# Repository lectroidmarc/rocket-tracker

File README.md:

# Rocket Tracker

This is the code for a [model rocket](https://en.wikipedia.org/wiki/Model_rocket) tracking system, to find (lost) model rockets via GPS.

The idea is that a GPS transmitter will live in a rocket and transmit data to a ground station via radio.  That ground station will then update a "cloud" based data store with the location(s) of the rocket(s).  A user (or users) can then access that data with any internet connected device (phone, tablet, laptop etc) to see the locations of their rockets.

Easy.

This system can be used by individuals for tracking one or more rockets or by large groups for tracking larger numbers of rockets.

The system is made up of the following components:

* ##### The GPS Transmitter

  The GPS transmitter is a small microcontroller that connects to a GPS and some kind of [XBee radio](http://www.digi.com/lp/xbee).  The micorcontroller parses the NMEA data from the GPS and transmits location data once per second over the radio.

  Transmission packets are 9 byte packets made up of a status byte then 4 bytes for latitude and 4 bytes for longitude (each are 4 byte floats).

* ##### The Ground Station

  The ground station listens for location messages from the transmitters and then forwards their location to a [Firebase](https://firebase.google.com) based database.

  If ZigBee radios are used, the ground station is also the network coordinator.

  The ground station code itself is a simple [NodeJS](https://nodejs.org/) app and so can run on anything that can run NodeJS and has a serial port to talk to an XBee radio.  And has internet access.

* ##### The Client App

  The client app is what the user uses to see the location of their rocket.  It connects to Firebase and displays the location data in (near) real time and allows the user to open the rocket's location in a mapping app.  Client web app code is located in the [gh-pages branch](../../tree/gh-pages) and can be seen at https://lectroidmarc.github.io/rocket-tracker/.

* ##### Dumb Relays (optional)

  If using ZigBee radios, every GPS transmitter is already a "router" but dedicated routers could also be added to extend range or enhance coverage.  These are simple ZigBee routers node that have no other logic to them, just powered pre-configured radios.

#### XBee Radio Setup

Generally speaking the only thing that needs to be changed from a factory default XBee radio is that they need to be placed into [API Mode 2](http://knowledge.digi.com/articles/Knowledge_Base_Article/What-is-API-Application-Programming-Interface-Mode-and-how-does-it-work).  Everything else can be handled in software.

For [ZigBee](https://en.wikipedia.org/wiki/ZigBee) radios, the proper ZigBee firmware (Coordinator, Router or End Device) will have to be installed.  For our purposes there's no advantage to the "End Device" firmware, so it's just one Coordinator and multiple Routers.

Note: Alternatively, settings (such as the PAN ID) can be pre-configured in each module.  In these cases, comment out the matching settings in the configuration file so they're not overwritten.

##### Dumb Relay nodes

Dumb relay nodes however should be configured in firmware with the PAN ID (`ATID`) and with Channel Verification turned on (`ATJV1`).

#### To Do

* The XBee protocols support status packets so the transmitter can use the lack of a successful status packet as a signal to enable some alternate means of discovery -- like enabling a loud buzzer after a certain timeout.

* Include some sort of built-in internet connectivity in the ground station.

* Expose the location data via a custom Bluetooth LE GATT profile on the ground station and allow the clients in range to use the [Web Bluetooth API](https://webbluetoothcg.github.io/web-bluetooth/) to fetch and display the data.  Note, with Bluetooth, _only one client can connect at a time_.

-30-

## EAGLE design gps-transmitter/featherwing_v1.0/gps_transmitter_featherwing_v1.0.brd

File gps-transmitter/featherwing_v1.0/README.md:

# GPS Transmitter M0 FeatherWing v1.0

These are [Eagle](http://www.autodesk.com/products/eagle/overview) files for a "FeatherWing", basically a sheild, for an [Adafruit Feather M0 Basic Proto](https://www.adafruit.com/products/2772) that supports both a XBee radio and an [Adafruit Ultimate GPS v3](https://www.adafruit.com/products/746).

Additionally the M0 BAT pin is tied to the GPS VBAT pin to enable hot start functionality.

Besides the Feather M0, Ultimate GPS and the appropriate XBee module, the following BOM is needed for a fully functioning FeatherWing

* 1x - [Short Feather Male Headers](https://www.adafruit.com/products/3002)
* 1x - [2mm 10 pin XBee Socket Headers](https://www.adafruit.com/products/366)
* 1x - [Standard 0.1" female headers](https://www.adafruit.com/products/598)
* 1x - [2-pin, 3.5mm pitch, screw terminal](https://www.adafruit.com/products/724)
* 2x56 (or M2) screws for mounting

-30-

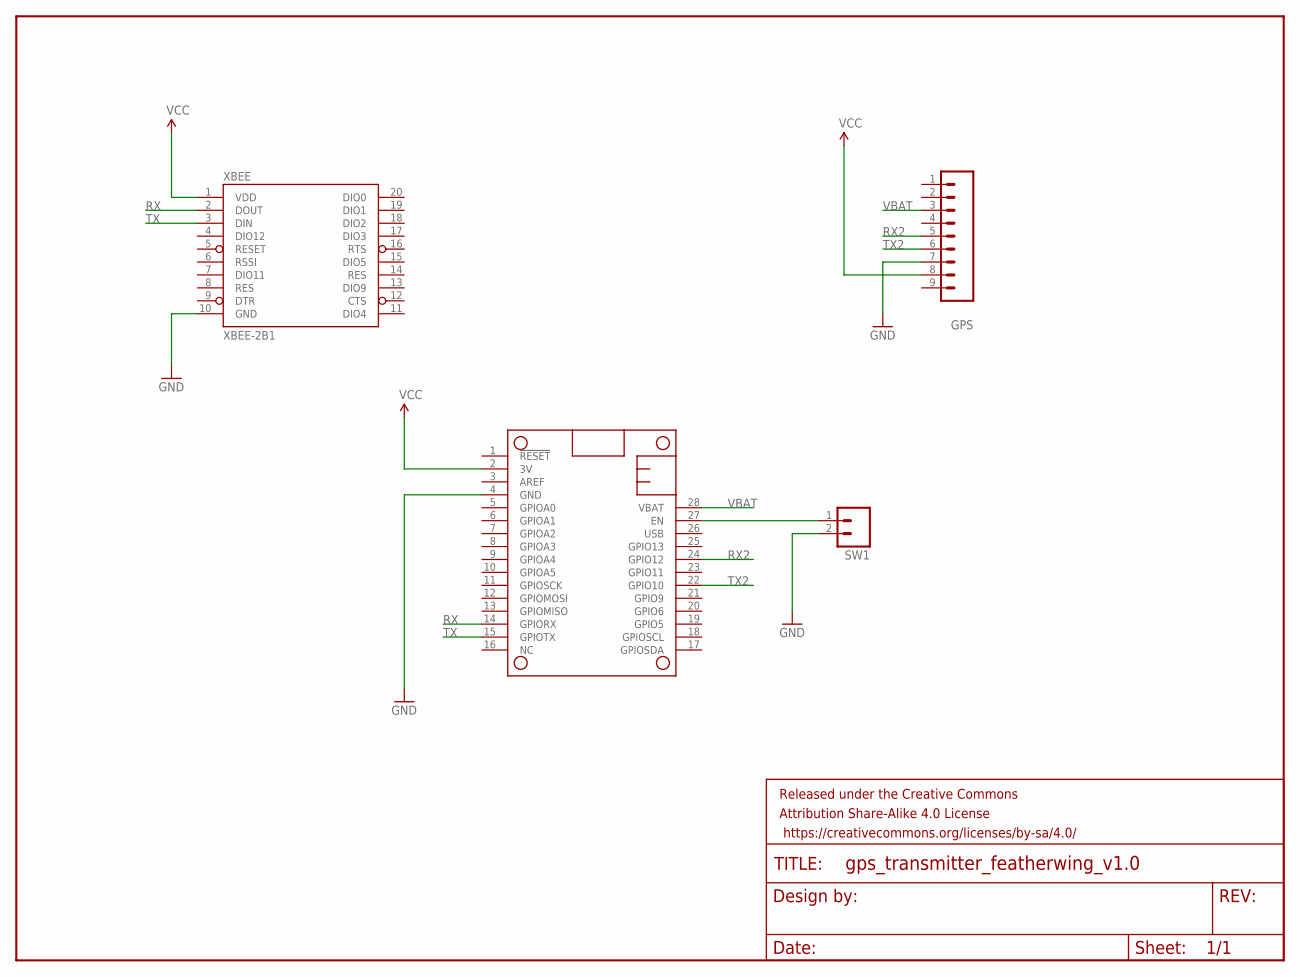
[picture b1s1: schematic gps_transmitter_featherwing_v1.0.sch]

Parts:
FRAME1: FRAME-LETTER; CREATIVE_COMMONS
GPS: M09; 1X09
MS1: FEATHERWING_NODIM; FEATHERWING_DIM
SW1: M023.5MM; SCREWTERMINAL-3.5MM-2
XBEE: XBEE-2B1; XBEE-1

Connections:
GND: GPS.7, MS1.4 (GND), SW1.2, XBEE.10 (GND)
unnamed: MS1.27 (EN), SW1.1
RX: MS1.14 (GPIORX), XBEE.2 (DOUT)
RX2: GPS.5, MS1.24 (GPIO12)
TX: MS1.15 (GPIOTX), XBEE.3 (DIN)
TX2: GPS.6, MS1.22 (GPIO10)
VBAT: GPS.3, MS1.28 (VBAT)
VCC: GPS.8, MS1.2 (3V), XBEE.1 (VDD)

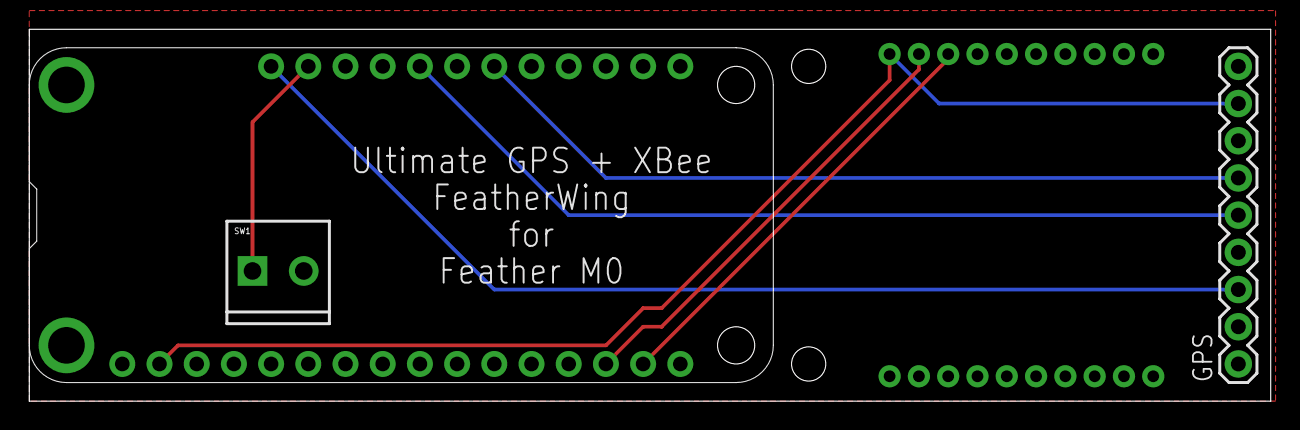
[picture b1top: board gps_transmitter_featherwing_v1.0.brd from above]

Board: 2 copper layers, 84.8 x 25.4 mm, 5 parts (1 on the bottom side), 8 nets.

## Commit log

2016-04-14 Initial commit of the rocket tracker system.
2016-04-14 First commit of the rocket-tracker client webapp.
2016-04-14 Add the Grunt based dev stuff.
2016-04-14 Clearer directory naming.
2016-04-14 More README updates.
2016-04-15 Fix the Grunt watch paths.
2016-04-15 Add pretty app icons.
2016-04-15 Use a Polymer helper function here.
2016-04-15 Avoid the FOUC on Safari.
2016-04-17 Slightly better editing functionality
2016-04-17 Update README.md
    Simplify this a bit.
2016-04-17 Update README.md
    Fix up the client blurb.
2016-04-17 Make the declatarion match reality.
2016-04-18 Support battery status.
    Use the next 3 bits after status to hold 8 battery modes.
2016-04-18 Support battery data.
2016-04-18 Add battery text too.
2016-04-18 Reflect the move to a Pi.
2016-04-18 Pi docs.
2016-04-18 Apple webapp-y stuff.
2016-04-19 More Webapp-y stuff.
2016-04-20 Add the 64 bit PAN ID bug fix.
2016-04-22 Add some serial port error checking.
2016-04-23 Fix the battery display.
2016-04-24 Better display on tablets.
2016-04-24 Pull the M0 code out of the feather_m0 branch.
2016-04-28 Support new Firebase structure.
2016-04-28 Update all the bower things.
2016-04-30 Add notes for this repo ;).
2016-04-30 Sudo is needed for this command on the Pi.
2016-05-01 Make hiding of cards persist.
    And throw on a way to unhide them.
2016-05-01 Better icon.
2016-05-01 Typo
2016-05-01 Update README.md
    Typos.
2016-05-01 Edit the README some more.
2016-05-02 Autohide the "Show Hidden Rockets" icon
2016-05-04 Fix the Rocket name on the map link.
2016-05-04 Change the logic for an "inactive" rocket a bit
2016-05-05 Huh, there's a linter for this stuff...
2016-05-06 Break out the geo-location stuff better.
2016-05-06 Update the bowers...
2016-05-08 Handle empty name values.
2016-05-22 Firebase v3
2016-12-20 Update all the Node things.
2016-12-20 Update the Pi docs for the latest Node.
2016-12-20 Update README.md
    Fix the spellings
2016-12-20 Update all the bowers.
2016-12-21 Confused by the LED macros...
2016-12-23 firebase-credentials -> serviceAccountKey
2016-12-23 More serviceAccountKey
2016-12-24 Use straight MDL instead of Polymer.
    Look, Polymer is neat and all, but the overhead was crazy. And like all things Javascript it has to completly redo itself every 2 years, breaking all the things that came before.
    What I'm trying to do here isn't hard, there was no need for all the silliness.
2016-12-24 Misc fixes for the new pages.
2016-12-24 Fix the fitting of the rockets.
2016-12-24 Center this thing in Snow Ranch.
    Because it's just right.
2016-12-24 Streetview is just not needed.
2016-12-24 Add hide/show support.
2016-12-24 Mobile Safari blows.
2016-12-24 Handle empty names.
2016-12-24 Default the card title to the ID.
2016-12-24 Use the GPS in mobiles devices.
    Looking at you, Chrome.
2016-12-29 Add support for authentication.
2016-12-30 Misc tweaks.
2016-12-31 Minor style tweak.
2016-12-31 Remove unneeded code.
2017-01-04 Show long distances in miles.
2017-01-05 Disable the 'show hidden' button when not needed.
2017-01-05 Add battery support back in.
2017-01-05 Float active rocket cards.
2017-01-06 Minor spacing.
2017-01-07 Improve battery reporting.
2017-01-07 Better battery reporting.
2017-01-07 Match the error lighting with the M0.
2017-01-07 Remove NMEA verifcation code.
    This was fixed in Adafruit GPS Library version 1.0.1.
2017-01-07 Sync up error reporting between the Fio and M0.
2017-01-07 One more comment/debug sync.
2017-01-10 Add sorting on the Rocket Name.
2017-01-11 Update comments.
2017-01-11 Update the distance in real time too.
2017-01-11 Add battery percentage.
2017-01-12 5 digits on the lat & lon, not 4.
2017-01-14 Fix overly broad CSS selectors. Make the percentage update.
2017-01-18 Don't let sorting mess with editing.
2017-01-19 Add Eagle design files for the first board.
2017-01-24 New radios may not have location data.
2017-01-24 A battery level of zero is not "undefined".
2017-01-29 Save hidden rockets between sessions.
2017-01-29 Fix map centering.
2017-01-29 Better handling of hidden rockets.
2017-01-31 Become a code Nazi.
2017-01-31 Sandbox code that doesn't need to be global.
2017-01-31 Remove extra linebreaks.
2017-02-01 Bump the maxListeners to avoid warnings.
2017-02-01 Defensive handling of metadata.
    This lets us maintain metatdata w/o matching rocket data.
2017-02-01 More highAccuracy.
2017-02-01 Revert unneeded code commit.
    It is too needed ;).
2017-02-01 Fix hiding bug.
2017-02-03 Add a short_name to the manifest.
2017-02-05 Add a Service Worker to make this more... app like
2017-02-05 Fix service worker path.
2017-02-05 Fix all the paths in the service worker.
2017-02-05 More Androidisms in the web app manifest
2017-02-06 JSCS tweaks.
2017-02-12 Apparently Google Maps hates caching?
2017-02-15 Bump library versions.
2017-03-07 Add a direction pointer if a heading is available.
    This was found to be neccessary at Snow Ranch where there's nothing to guage location on in the map view.
2017-03-12 Improved battery reporting.
2017-03-12 Actually stay at 50% battery :/
2017-04-26 Switch over to the v1 Web Components.
2017-04-27 Minor tweaks.
2017-04-27 latest Firebase.
2017-04-27 Roboto.
2017-04-27 CSS vars.
2017-04-27 More ES6 goodness.
2017-04-27 Add some jshint and jscs to this guy.
2017-04-28 Remove unused CSS.
2017-04-28 Still more unneeded CSS.
2017-04-28 More unneeded CSS.
2017-04-28 Bump the cache version for the new CSS changes.
2017-04-28 Style nit
2017-04-29 Bump the cache version number.
2017-05-05 IDs should not begin with numbers.
2017-05-22 Minor Lighthouse tweaks.
2017-05-22 Bump cache version.
2017-05-29 GPS update rate.
    Add (commented) lines for tweaking the GPS update rate.
2017-06-13 Update to latest Firebase.
2017-07-06 Some more ES6
2017-07-07 Better Es6 ifying
2017-07-08 Ignore VScode
2017-07-15 Misc cleanup.
2017-08-19 Update for newer NodeJS
2018-01-14 Update serialport and xbee-api
2018-01-18 Switch to eslint
2018-11-27 Fix GitHub security warnings.
2018-11-27 Ignore building directory from the pages.
2019-06-01 Silence node security warnings.
2019-06-01 Silence security warnings and update for Node 10
2019-06-01 Silence still more security errors...
2019-08-20 Fix lodash security
2020-04-16 Bump https-proxy-agent from 2.2.2 to 2.2.4 in /ground-station/node
    Bumps [https-proxy-agent](https://github.com/TooTallNate/node-https-proxy-agent) from 2.2.2 to 2.2.4.
    - [Release notes](https://github.com/TooTallNate/node-https-proxy-agent/releases)
    - [Commits](https://github.com/TooTallNate/node-https-proxy-agent/compare/2.2.2...2.2.4)
2020-06-06 Bump websocket-extensions from 0.1.3 to 0.1.4 in /ground-station/node
    Bumps [websocket-extensions](https://github.com/faye/websocket-extensions-node) from 0.1.3 to 0.1.4.
    - [Release notes](https://github.com/faye/websocket-extensions-node/releases)
    - [Changelog](https://github.com/faye/websocket-extensions-node/blob/master/CHANGELOG.md)
    - [Commits](https://github.com/faye/websocket-extensions-node/compare/0.1.3...0.1.4)
2020-07-30 Bump dot-prop from 5.1.0 to 5.2.0 in /ground-station/node
    Bumps [dot-prop](https://github.com/sindresorhus/dot-prop) from 5.1.0 to 5.2.0.
    - [Release notes](https://github.com/sindresorhus/dot-prop/releases)
    - [Commits](https://github.com/sindresorhus/dot-prop/compare/v5.1.0...v5.2.0)
2020-09-11 Bump node-fetch from 2.6.0 to 2.6.1 in /ground-station/node
    Bumps [node-fetch](https://github.com/bitinn/node-fetch) from 2.6.0 to 2.6.1.
    - [Release notes](https://github.com/bitinn/node-fetch/releases)
    - [Changelog](https://github.com/node-fetch/node-fetch/blob/master/docs/CHANGELOG.md)
    - [Commits](https://github.com/bitinn/node-fetch/compare/v2.6.0...v2.6.1)
2020-12-10 Bump ini from 1.3.5 to 1.3.7 in /ground-station/node
    Bumps [ini](https://github.com/isaacs/ini) from 1.3.5 to 1.3.7.
    - [Release notes](https://github.com/isaacs/ini/releases)
    - [Commits](https://github.com/isaacs/ini/compare/v1.3.5...v1.3.7)
2021-04-23 Edison... _pish_
2021-04-23 Also: Edison... _pish_
2021-04-23 Update a lot of Node stuff, so this guy still builds.
2021-04-23 Node is built-in now.
2022-04-09 Bump minimist from 1.2.5 to 1.2.6 in /ground-station/node
    Bumps [minimist](https://github.com/substack/minimist) from 1.2.5 to 1.2.6.
    - [Release notes](https://github.com/substack/minimist/releases)
    - [Commits](https://github.com/substack/minimist/compare/1.2.5...1.2.6)
    ---
    updated-dependencies:
    - dependency-name: minimist
2022-06-02 Bump protobufjs from 6.10.2 to 6.11.3 in /ground-station/node
    Bumps [protobufjs](https://github.com/protobufjs/protobuf.js) from 6.10.2 to 6.11.3.
    - [Release notes](https://github.com/protobufjs/protobuf.js/releases)
    - [Changelog](https://github.com/protobufjs/protobuf.js/blob/v6.11.3/CHANGELOG.md)
    - [Commits](https://github.com/protobufjs/protobuf.js/compare/v6.10.2...v6.11.3)
    ---
    updated-dependencies:
2022-06-25 Bump node-fetch from 2.6.1 to 2.6.7 in /ground-station/node
    Bumps [node-fetch](https://github.com/node-fetch/node-fetch) from 2.6.1 to 2.6.7.
    - [Release notes](https://github.com/node-fetch/node-fetch/releases)
    - [Commits](https://github.com/node-fetch/node-fetch/compare/v2.6.1...v2.6.7)
    ---
    updated-dependencies:
    - dependency-name: node-fetch
2023-01-09 Bump jsonwebtoken and firebase-admin in /ground-station/node
    Bumps [jsonwebtoken](https://github.com/auth0/node-jsonwebtoken) to 9.0.0 and updates ancestor dependency [firebase-admin](https://github.com/firebase/firebase-admin-node). These dependencies need to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
    Updates `jsonwebtoken` from 8.5.1 to 9.0.0
    - [Release notes](https://github.com/auth0/node-jsonwebtoken/releases)
    - [Changelog](https://github.com/auth0/node-jsonwebtoken/blob/master/CHANGELOG.md)
    - [Commits](https://github.com/auth0/node-jsonwebtoken/compare/v8.5.1...v9.0.0)
    Updates `firebase-admin` from 9.6.0 to 11.4.1
2023-03-04 Bump minimist from 1.2.5 to 1.2.8 in /ground-station/node
    Bumps [minimist](https://github.com/minimistjs/minimist) from 1.2.5 to 1.2.8.
    - [Release notes](https://github.com/minimistjs/minimist/releases)
    - [Changelog](https://github.com/minimistjs/minimist/blob/main/CHANGELOG.md)
    - [Commits](https://github.com/minimistjs/minimist/compare/v1.2.5...v1.2.8)
    ---
    updated-dependencies:

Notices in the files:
parts and their libraries:
SparkFun-Aesthetics: Licensing: Creative Commons ShareAlike 4.0 International - https://creativecommons.org/licenses/by-sa/4.0
SparkFun-Aesthetics: Released under the Creative Commons Attribution Share-Alike 4.0 License
SparkFun-Aesthetics: https://creativecommons.org/licenses/by-sa/4.0
